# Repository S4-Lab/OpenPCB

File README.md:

# 💥OpenPCB: Manufacturing Double Layer PCBs Using Commodity Laser Engraver💥
This guide shows you how to manufacture a double layer PCB with vias and through holes using a relatively low cost (<$2k) commodity fiber laser engraver (ComMarker B4 20W). We provide custom enclosure design files to improve the safety of the engraver as well as 3D-printable clamp rigs to enable repeatable lasing operations on both sides of the PCB with minimal tuning.
## Video Guide:
<p align="center">
  
</p>

## Equipment Needed:

| Name | Description | Amount | Vendor |
| :---: | :---: | :---: | :---: |
| ComMarker B4 20W | Fiber laser engraver | 1 | [ComMarker](https://commarker.com/product/b4-laser-engraver/) |
| ComMarker Fume Extractor-100W | Extracts fumes from the enclosure | 1 | [ComMarker](https://commarker.com/product/commarker-fume-extractor-100w/) |
| 24V LED Strip | Illuminates the inside of the enclosure | 1 | [Amazon](https://www.amazon.com/dp/B0D8L9HJXN) |
| 24V Warning Light | Indicates the machine is on for general compliance purposes | 1 | [Amazon](https://www.amazon.com/dp/B06XKLY1N2) |
| UV Curing Light | UV light for curing soldermask ink | 1 | [Amazon](https://www.amazon.com/dp/B075GWKN83) |
| 1/16" Sheet Aluminum | Sheet metal for the enclosure | 1 | [McMaster-Carr](https://www.mcmaster.com/products/aluminum-extrusions/shape~sheet/multipurpose-6061-aluminum-sheets-and-bars-7/) |
| Self-Centering Vise | Vise for holding the PCB centered in the rig | 1 | [Amazon](https://www.amazon.com/dp/B0CKW946NN) |
| M5x6 mm Shoulder Bolts 5 pcs | Locating screws for the vise | 1 | [Amazon](https://www.amazon.com/dp/B077GX37SX) |
| Aluminum Tape | Tape for sealing around the enclosure to prevent light from exiting | 1 | [Amazon](https://www.amazon.com/Aluminum-Ductwork-Temperature-Insulation-Adhesive/dp/B0B6NDFXPN/ref=sr_1_1_sspa?sr=8-1-spons&sp_csd=d2lkZ2V0TmFtZT1zcF9hdGY&psc=1)
| Safety Shield | Front door | 1 | [ComMarker](https://commarker.com/product/laser-engraver-enclosure-green/?utm_source=Google%20Shopping&utm_campaign=Google%20Shopping%20Feed%20US&utm_medium=cpc&utm_term=23539&gad_source=1&gad_campaignid=21084642396&gbraid=0AAAAAqD6U5Hp8d97pg5T4UTTmunvMlgEU&gclid=Cj0KCQjw-NfDBhDyARIsAD-ILeC8pDan2KiLlLADY5TseprIdRYGhm98cP78Yc0IAMmq2-XbsZg_NHcaAm9cEALw_wcB)
| Metric Bolt Assortment | Use M5 for general assembly. M3 for hinges | 1 | [Amazon](https://www.amazon.com/dp/B0CF9HRPC8) 
| Neodymium Magnets | Door latching | 1 | [Amazon](https://www.amazon.com/dp/B0CF9HRPC8) |
| Trash Bag | Back opening sealer | 1 | [Amazon](https://www.amazon.com/Glad-ForceFlex-Kitchen-Pine-Sol-Original/dp/B0D6CWK6F9/ref=sr_1_3_sspa?crid=5R2B6UYB47ME&dib=eyJ2IjoiMSJ9.L7lzwJ7FSDRUV-HmHDK3y1Pb2_EUIoTHHzdCQtD415yel2aLij75bSLqcW84EfRqn-jszuEkq57lRTnM5KtSEl34UnSsr0zT5cMXwAO7aCYf9FdHl-0u_dra-MiqyeoemIPHIJ2zwIb8MGofQbn2d3ybZqIKfhLvVKX0ist--CTJOdxzY1T8KQOokAvh_QZZOSk4s67wYPl9tNKWXDk2zGQtNKydY3OgjQTBVWAoy7tpKaH_IIWrAWKgWBABSgjXrvKzyy11tvM3QKLakqQeiqWeFO7voVIYK97dFNKF1g8.U8PH-uSUzZQAuDlWCfxipwKteU5tKV7bkj7nphp5fe4&dib_tag=se&keywords=trash+bag&qid=1752606252&sprefix=trash+bag%2Caps%2C190&sr=8-3-spons&sp_csd=d2lkZ2V0TmFtZT1zcF9hdGY&psc=1) |

## Laser Engraving SOP
See the [Laser Engraver SOP Notion page](https://brave-paprika-311.notion.site/Laser-Engraver-SOP-2229387ccfca80dc991dc07f11edf8c1?source=copy_link) on how to fabricate your own PCBs!

## Credit
- [Stephen Hawes](https://youtu.be/wAiGCyZZq6w?feature=shared)
- [Electronoobs](https://youtu.be/PoYcjyghDx4?feature=shared)

This guide is brought to you by [Teresa Perez](https://www.linkedin.com/in/teresa23perez/) and [Bill Yen](https://billyen33.com)

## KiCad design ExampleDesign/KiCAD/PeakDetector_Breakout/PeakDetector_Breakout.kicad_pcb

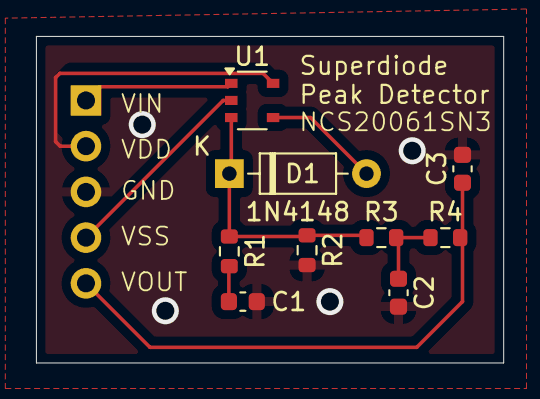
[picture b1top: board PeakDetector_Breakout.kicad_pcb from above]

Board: 2 copper layers, 26.0 x 18.1 mm, 10 parts (1 on the bottom side), 9 nets.

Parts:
C1: c=220n; C_0603_1608Metric
C2, C3: c=100n; C_0603_1608Metric
D1: 1N4148; D_DO-35_SOD27_P7.62mm_Horizontal
J2: Conn_01x05_Pin; PinHeader_1x05_P2.54mm_Vertical
R1: r=100; R_0603_1608Metric
R2: r=332k; R_0603_1608Metric
R3, R4: r=100k; R_0603_1608Metric
U1: TSOP-5_1.65x3.05mm_P0.95mm

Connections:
0: C1.2, C2.2, C3.2, J2.3, R2.2
/VIN: J2.1, U1.1 (+)
/VOUT: C3.1, J2.5, R4.2
/V_peak: D1.1 (K), R1.1, R2.1, R3.1, U1.3 (-)
unnamed: C1.1, R1.2
unnamed: C2.1, R3.2, R4.1
unnamed: D1.2 (A), U1.4 (OUT)
VDD: J2.2, U1.5 (V+)
VSS: J2.4, U1.2 (V-)

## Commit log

2025-07-15 Added example files
2025-07-15 Added Images
2025-07-15 Create LICENSE
